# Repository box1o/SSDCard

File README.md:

# SSDCard 

## SmartCard emulator in formfactor of a common Card.
- Size : 85.60 mm × 53.98 mm / reference : ISO/IEC 7810 ID-1 + 50 mm  to the width for the pcb components
- Thickness : 0.76 mm or based on the pcb manufacturer's capabilities

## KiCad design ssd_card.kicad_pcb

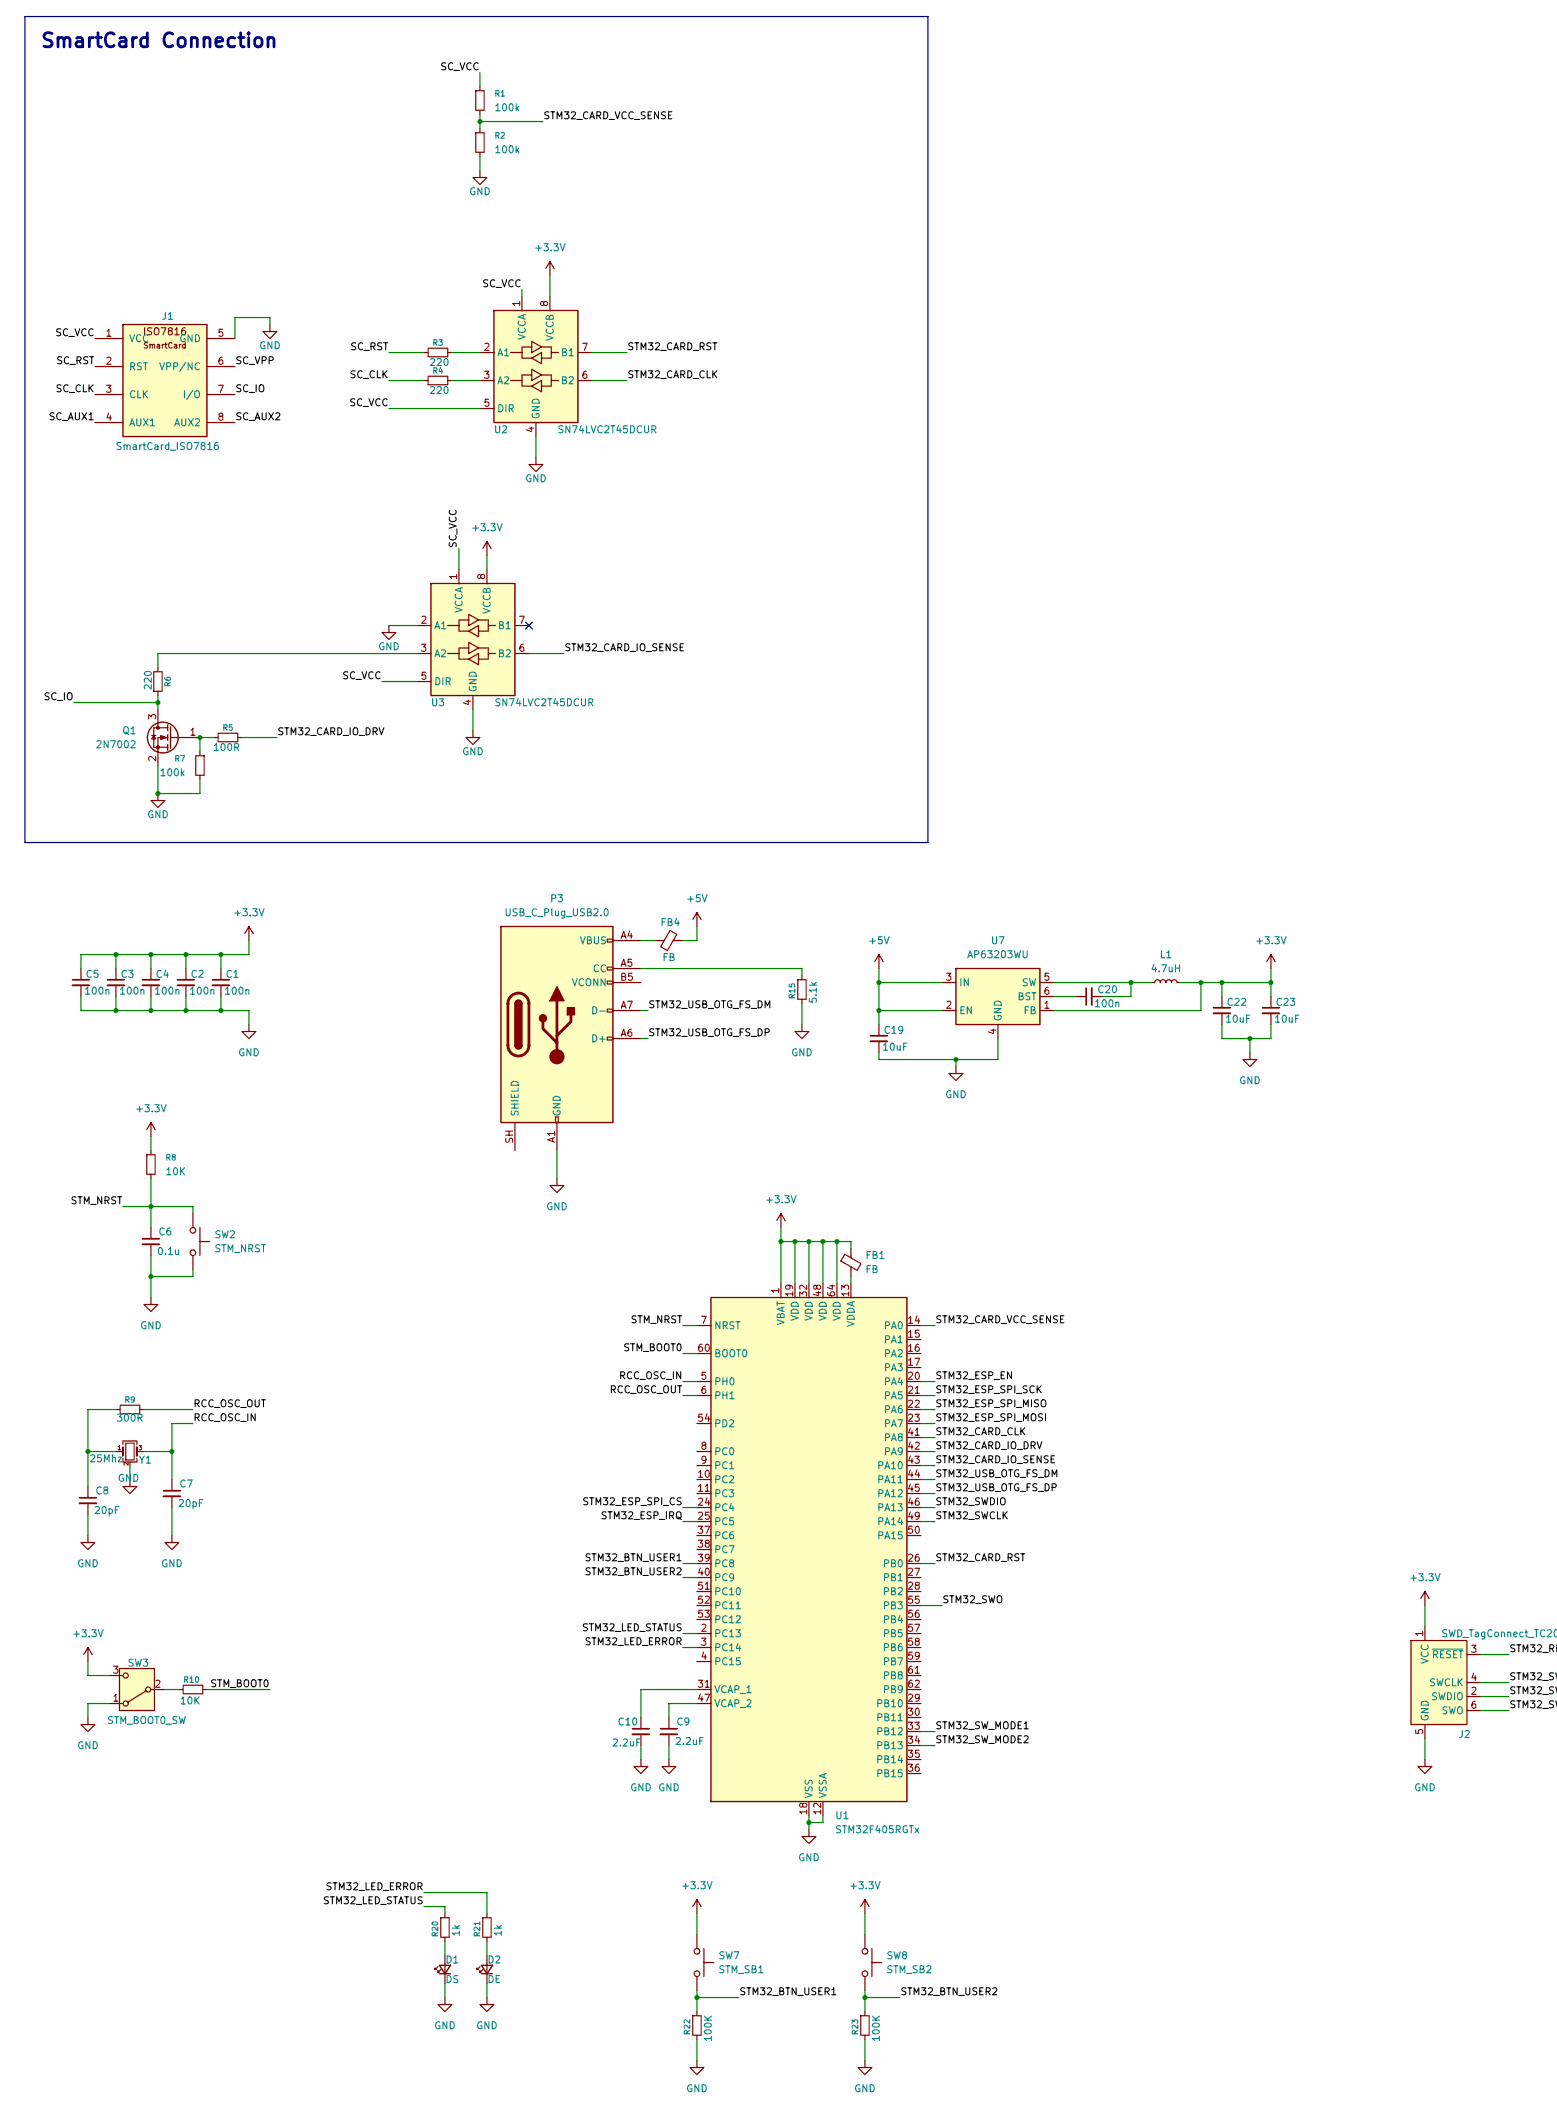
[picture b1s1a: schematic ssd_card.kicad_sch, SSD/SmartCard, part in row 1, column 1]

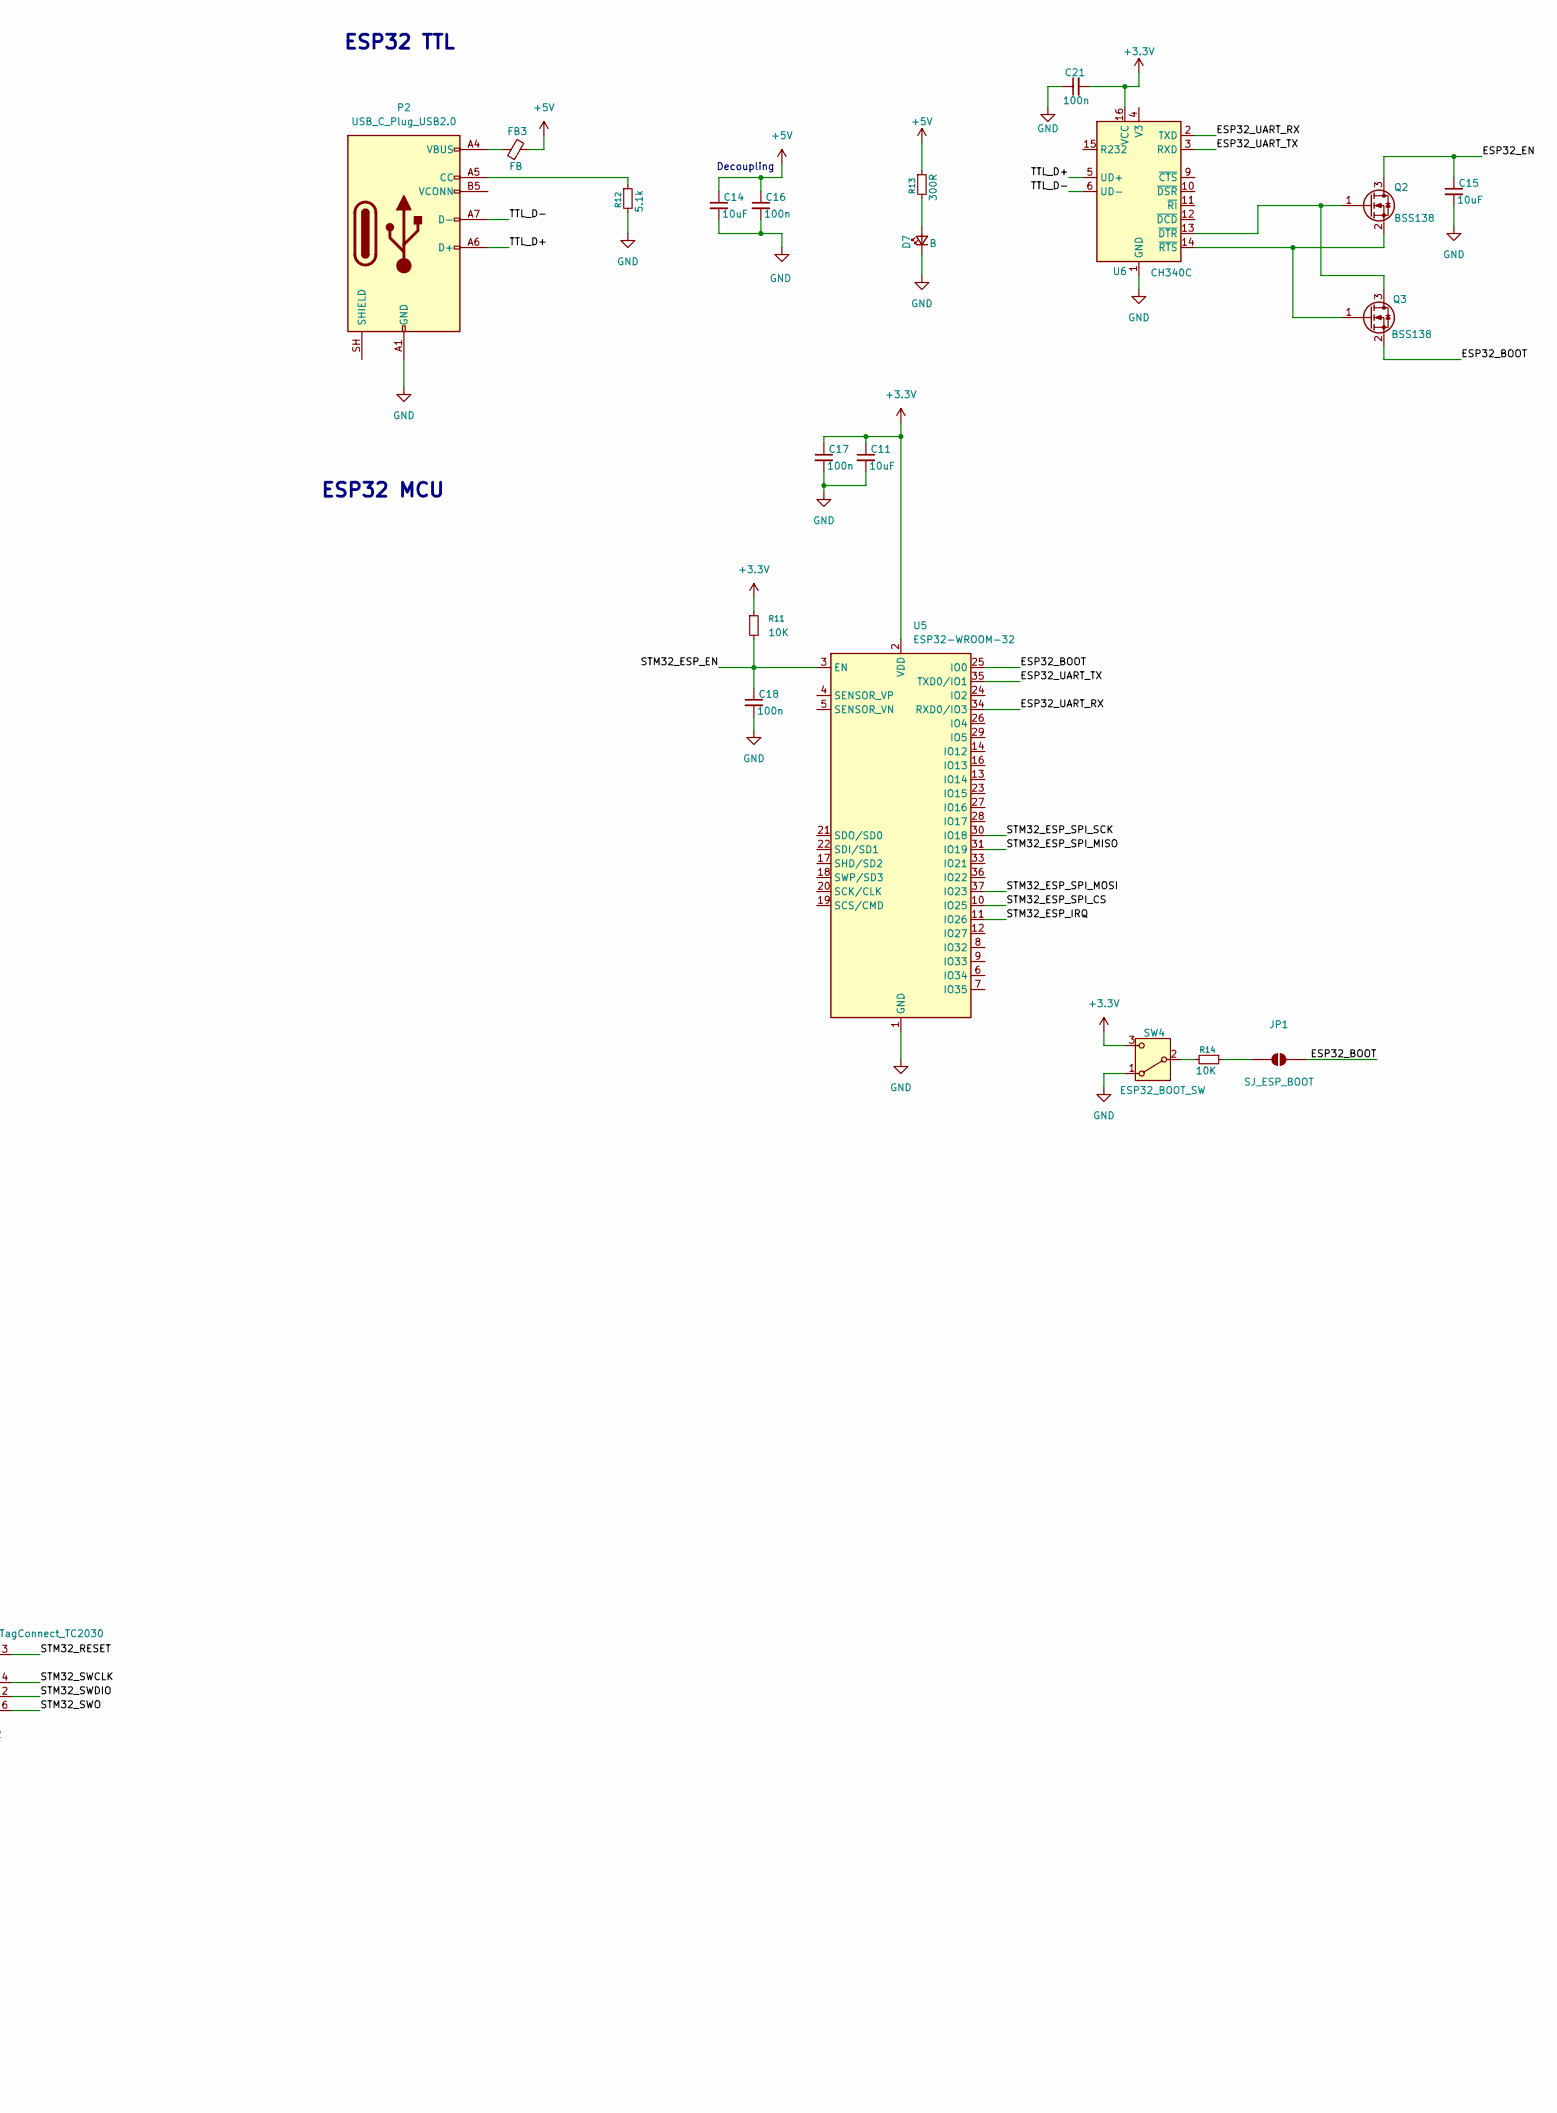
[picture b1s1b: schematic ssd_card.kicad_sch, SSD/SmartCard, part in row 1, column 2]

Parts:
C1, C2, C3, C4, C5, C16, C17, C18, C20, C21: 100n; C_0603_1608Metric
C6: 0.1u; C_0603_1608Metric
C7, C8: 20pF; C_0603_1608Metric
C9, C10: 2.2uF; C_0603_1608Metric
C11, C14, C15, C19, C22, C23: 10uF; C_0603_1608Metric
D1: DS; LED_0603_1608Metric
D2: DE; LED_0603_1608Metric
D7: B; LED_0603_1608Metric
FB1, FB3, FB4: FB; L_0805_2012Metric
J1: SmartCard_ISO7816; ISO7816_CardPads_Clean_Functional
J2: SWD_TagConnect_TC2030; Tag-Connect_TC2030-IDC-NL_2x03_P1.27mm_Vertical
JP1: SJ_ESP_BOOT; SolderJumper-2_P1.3mm_Open_RoundedPad1.0x1.5mm
L1: 4.7uH; L_0805_2012Metric
P2, P3: USB_C_Plug_USB2.0; USB_C_Receptacle_HRO_TYPE-C-31-M-12
Q1: 2N7002; SOT-23
Q2, Q3: BSS138; SOT-23
R1, R2, R7: 100k; R_0603_1608Metric
R3, R4, R6: 220; R_0603_1608Metric
R5: 100R; R_0603_1608Metric
R8, R10, R11, R14: 10K; R_0603_1608Metric
R9, R13: 300R; R_0603_1608Metric
R12, R15: 5.1k; R_0603_1608Metric
R20, R21: 1k; R_0603_1608Metric
R22, R23: 100K; R_0603_1608Metric
SW2: STM_NRST; SW_SPST_B3U-1000P
SW3: STM_BOOT0_SW; SW_SPDT_PCM12
SW4: ESP32_BOOT_SW; SW_SPDT_PCM12
SW7: STM_SB1; SW_SPST_B3U-1000P
SW8: STM_SB2; SW_SPST_B3U-1000P
U1: STM32F405RGTx; LQFP-64_10x10mm_P0.5mm
U2, U3: SN74LVC2T45DCUR; VSSOP-8_2.3x2mm_P0.5mm
U5: ESP32-WROOM-32
U6: CH340C; SOIC-16_3.9x9.9mm_P1.27mm
U7: AP63203WU; TSOT-23-6
Y1: 25Mhz

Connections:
+3.3V: C1.1, C2.1, C3.1, C4.1, C5.1, C11.1, C17.1, C21.2, C22.1, C23.1, FB1.1, J2.1 (VCC), L1.2, R8.1, R11.1, SW3.3 (C), SW4.3 (C), SW7.1, SW8.1, U1.1 (VBAT), U1.19 (VDD), U1.32 (VDD), U1.48 (VDD), U1.64 (VDD), U2.8 (VCCB), U3.8 (VCCB), U5.2 (VDD), U6.16 (VCC), U7.1 (FB)
+5V: C14.1, C16.1, C19.1, FB3.2, FB4.2, R13.1, U7.2 (EN), U7.3 (IN)
/ESP32_BOOT: JP1.2 (B), Q3.2 (S), U5.25 (IO0)
/ESP32_EN: C15.1, Q2.3 (D)
/ESP32_UART_RX: U5.34 (RXD0/IO3), U6.2 (TXD)
/ESP32_UART_TX: U5.35 (TXD0/IO1), U6.3 (RXD)
/RCC_OSC_IN: C7.1, U1.5 (PH0), Y1.3
/RCC_OSC_OUT: R9.1, U1.6 (PH1)
/SC_AUX1: J1.4 (AUX1)
/SC_AUX2: J1.8 (AUX2)
/SC_CLK: J1.3 (CLK), R4.1
/SC_IO: J1.7 (I/O), Q1.3 (D), R6.1
/SC_RST: J1.2 (RST), R3.1
/SC_VCC: J1.1 (VCC), R1.1, U2.1 (VCCA), U2.5 (DIR), U3.1 (VCCA), U3.5 (DIR)
/SC_VPP: J1.6 (VPP/NC)
/STM32_BTN_USER1: R22.1, SW7.2, U1.39 (PC8); also elsewhere on the board
/STM32_BTN_USER2: R23.1, SW8.2, U1.40 (PC9); also elsewhere on the board
/STM32_CARD_CLK: U1.41 (PA8), U2.6 (B2)
/STM32_CARD_IO_DRV: R5.1, U1.42 (PA9)
/STM32_CARD_IO_SENSE: U1.43 (PA10), U3.6 (B2)
/STM32_CARD_RST: U1.26 (PB0), U2.7 (B1)
/STM32_CARD_VCC_SENSE: R1.2, R2.1, U1.14 (PA0)
/STM32_ESP_EN: C18.1, R11.2, U1.20 (PA4), U5.3 (EN)
/STM32_ESP_IRQ: U1.25 (PC5), U5.11 (IO26)
/STM32_ESP_SPI_CS: U1.24 (PC4), U5.10 (IO25)
/STM32_ESP_SPI_MISO: U1.22 (PA6), U5.31 (IO19)
/STM32_ESP_SPI_MOSI: U1.23 (PA7), U5.37 (IO23)
/STM32_ESP_SPI_SCK: U1.21 (PA5), U5.30 (IO18)
/STM32_LED_ERROR: R21.1, U1.3 (PC14)
/STM32_LED_STATUS: R20.1, U1.2 (PC13)
/STM32_RESET: J2.3 (~RESET)
/STM32_SWCLK: J2.4 (SWCLK), U1.49 (PA14)
/STM32_SWDIO: J2.2 (SWDIO), U1.46 (PA13)
/STM32_SWO: J2.6 (SWO), U1.55 (PB3)
/STM32_SW_MODE1: U1.33 (PB12)
/STM32_SW_MODE2: U1.34 (PB13)
/STM32_USB_OTG_FS_DM: P3.A7 (D-), U1.44 (PA11)
/STM32_USB_OTG_FS_DP: P3.A6 (D+), U1.45 (PA12)
/STM_BOOT0: R10.1, U1.60 (BOOT0)
/STM_NRST: C6.1, R8.2, SW2.1, U1.7 (NRST)
/TTL_D+: P2.A6 (D+), U6.5 (UD+)
/TTL_D-: P2.A7 (D-), U6.6 (UD-)
GND: C1.2, C2.2, C3.2, C4.2, C5.2, C6.2, C7.2, C8.2, C9.2, C10.2, C11.2, C14.2, C15.2, C16.2, C17.2, C18.2, C19.2, C21.1, C22.2, C23.2, D1.1 (K), D2.1 (K), D7.1 (K), J1.5 (GND), J2.5 (GND), P2.A1 (GND), P2.A12 (GND), P2.B1 (GND), P2.B12 (GND), P3.A1 (GND), P3.A12 (GND), P3.B1 (GND), P3.B12 (GND), Q1.2 (S), R2.2, R7.2, R12.2, R15.2, R22.2, R23.2, SW2.2, SW3.1 (A), SW4.1 (A), U1.12 (VSSA), U1.18 (VSS), U1.63 (VSS), U2.4 (GND), U3.2 (A1), U3.4 (GND), U5.1 (GND), U5.15 (GND), U5.38 (GND), U5.39 (GND), U6.1 (GND), U7.4 (GND), Y1.2 (G), Y1.4 (G)
unnamed: C8.1, R9.2, Y1.1
unnamed: D1.2 (A), R20.2
unnamed: D2.2 (A), R21.2
unnamed: D7.2 (A), R13.2
unnamed: FB3.1, P2.A4 (VBUS), P2.A9 (VBUS), P2.B4 (VBUS), P2.B9 (VBUS)
unnamed: FB4.1, P3.A4 (VBUS), P3.A9 (VBUS), P3.B4 (VBUS), P3.B9 (VBUS)
unnamed: JP1.1 (A), R14.1
unnamed: P2.A5 (CC), R12.1
unnamed: P3.A5 (CC), R15.1
unnamed: Q1.1 (G), R5.2, R7.1
unnamed: Q2.1 (G), Q3.3 (D), U6.13 (~DTR)
unnamed: Q2.2 (S), Q3.1 (G), U6.14 (~RTS)
unnamed: R10.2, SW3.2 (B)
unnamed: R14.2, SW4.2 (B)
unnamed: C10.1, U1.31 (VCAP_1)
unnamed: C9.1, U1.47 (VCAP_2)
unnamed: FB1.2, U1.13 (VDDA)
unnamed: R3.2, U2.2 (A1)
unnamed: R4.2, U2.3 (A2)
unnamed: R6.2, U3.3 (A2)
unnamed: C20.1, U7.6 (BST)
unnamed: C20.2, L1.1, U7.5 (SW)

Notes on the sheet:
SmartCard Connection
ESP32 TTL
Decoupling
ESP32 MCU

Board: 2 copper layers, 68 parts (0 on the bottom side), 59 nets, no tracks yet.

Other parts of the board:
R18, R19: 10K; R_0603_1608Metric

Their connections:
/STM32_BTN_USER1: R18.1; also elsewhere on the board
/STM32_BTN_USER2: R19.1; also elsewhere on the board

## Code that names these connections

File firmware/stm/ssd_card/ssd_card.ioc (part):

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Mcu.Name=STM32F405RGTx
Mcu.Package=LQFP64
Mcu.UserName=STM32F405RGTx
PA0-WKUP.GPIOParameters=GPIO_Label
PA0-WKUP.GPIO_Label=CARD_VCC_SENSE
PA0-WKUP.Signal=ADCx_IN0
PA10.GPIOParameters=GPIO_Label
PA10.GPIO_Label=CARD_IO_SENSE
PA10.Signal=GPIO_Input
PA11.Mode=Device_Only
PA11.Signal=USB_OTG_FS_DM
PA12.Mode=Device_Only
PA12.Signal=USB_OTG_FS_DP
PA13.Mode=Trace_Asynchronous_SW
PA13.Signal=SYS_JTMS-SWDIO
PA14.Mode=Trace_Asynchronous_SW
PA14.Signal=SYS_JTCK-SWCLK
PA4.GPIOParameters=GPIO_Label
PA4.GPIO_Label=ESP_EN
PA4.Signal=GPIO_Output
PA5.GPIOParameters=GPIO_Label
PA5.GPIO_Label=ESP_SPI_SCK
PA5.Mode=Full_Duplex_Master
PA5.Signal=SPI1_SCK
PA6.GPIOParameters=GPIO_Label
PA6.GPIO_Label=ESP_SPI_MISO
PA6.Mode=Full_Duplex_Master
PA6.Signal=SPI1_MISO
PA7.GPIOParameters=GPIO_Label
PA7.GPIO_Label=ESP_SPI_MOSI
PA7.Mode=Full_Duplex_Master
PA7.Signal=SPI1_MOSI
PA8.GPIOParameters=GPIO_Label
PA8.GPIO_Label=CARD_CLK
PA8.Signal=S_TIM1_CH1
PA9.GPIOParameters=PinState,GPIO_Label
PA9.GPIO_Label=CARD_IO_DRV
PA9.PinState=GPIO_PIN_SET
PA9.Signal=GPIO_Output
PB0.GPIOParameters=GPIO_Label
PB0.GPIO_Label=CARD_RST
PB0.Signal=GPXTI0
PB12.GPIOParameters=GPIO_Label
PB12.GPIO_Label=SW_MODE1
PB12.Signal=GPXTI12
PB13.GPIOParameters=GPIO_Label
PB13.GPIO_Label=SW_MODE2
PB13.Signal=GPXTI13
PB3.Mode=Trace_Asynchronous_SW
PB3.Signal=SYS_JTDO-SWO
PC13-ANTI_TAMP.GPIOParameters=GPIO_Label
PC13-ANTI_TAMP.GPIO_Label=LED_STATUS
PC13-ANTI_TAMP.Signal=GPIO_Analog
PC14-OSC32_IN.GPIOParameters=GPIO_Label
PC14-OSC32_IN.GPIO_Label=LED_ERROR
PC14-OSC32_IN.Signal=GPIO_Output
PC4.GPIOParameters=GPIO_Label
PC4.GPIO_Label=ESP_SPI_CS
PC4.Signal=GPIO_Analog
PC5.GPIOParameters=GPIO_Label
PC5.GPIO_Label=ESP_IRQ
PC5.Signal=GPXTI5
PC8.GPIOParameters=GPIO_Label
PC8.GPIO_Label=BTN_USER1
PC8.Signal=GPXTI8
PC9.GPIOParameters=GPIO_Label
PC9.GPIO_Label=BTN_USER2
PC9.Signal=GPXTI9
PH0-OSC_IN.Mode=HSE-External-Oscillator
PH0-OSC_IN.Signal=RCC_OSC_IN
PH1-OSC_OUT.Mode=HSE-External-Oscillator
PH1-OSC_OUT.Signal=RCC_OSC_OUT
RCC.HSE_VALUE=25000000
RCC.SYSCLKFreq_VALUE=168000000
RCC.SYSCLKSource=RCC_SYSCLKSOURCE_PLLCLK
board=custom

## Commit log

2026-05-24 feat: add ISO 7816 card outline boundaries and pad symbols
2026-05-24 fix: vendor smartcard KiCad library
2026-05-24 fix: use valid release tag prefix
2026-05-24 docs: fix release render link
2026-05-24 ci: trigger PCB release from dev
2026-05-24 feat: STM32 firmware/pin config
2026-05-24 feat: STM32 start schematic
2026-05-25 feat: Documentation
2026-05-25 feat: iso7816
2026-05-26 ci: make PCB release manual only
2026-05-26 Add HRO USB-C receptacle footprint
